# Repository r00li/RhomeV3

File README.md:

Rhome V3
=========

Rhome V3 is a stand-alone ARM based room automation system. It features:

  - (Wireless) Light control
  - Window blind control
  - Local LCD based GUI
  - Wireless remote control (for now 433MHz remotes only)
  - Wifi connectivity
  - Easy to use web control interface (integrated web server)

It runs on a standard STM32F4 Cortex M4 microcontroller. This project includes all the necessary source code (EMBLOCKS PROJECT folder) and eagle board files with schematics (SCHEMATIC folder). I will also add .stl files for a 3D printed case later.

Changelog
----

0.1:

This is an alpha release and needs a lot of code cleanup. More details on how to set eveything up are comming later.

Requirements
-----------

You will need the following things to get this running:

  - A built and ready Rhome V3 PCB (or an STM32F4 discovery board with necessary components connected)
  - A sailwinch servo for each window blind that you want to control (more details are comming later)
  - A wireless 433MHz switch for each light that you want to control (I am using ones made by Intertechno, but others should work)
  - An STM32F4 Discovery board for programming (anything with STLINK should work though)
  - 5V power supply (computer USB port should work though some have trouble powering the PCB with servo motors attached)
  - A running installation of em::blocks IDE (open source, very easy to use) for compiling and uploading the project to the board

After that you just need is to connect your STLINK programmer to the programming interface on the board, select release in the em::blocks IDE and upload the code to the board. All the configuration is done through the integrated GUI.

License
----

GNU GPL v3 - see LICENSE for more details

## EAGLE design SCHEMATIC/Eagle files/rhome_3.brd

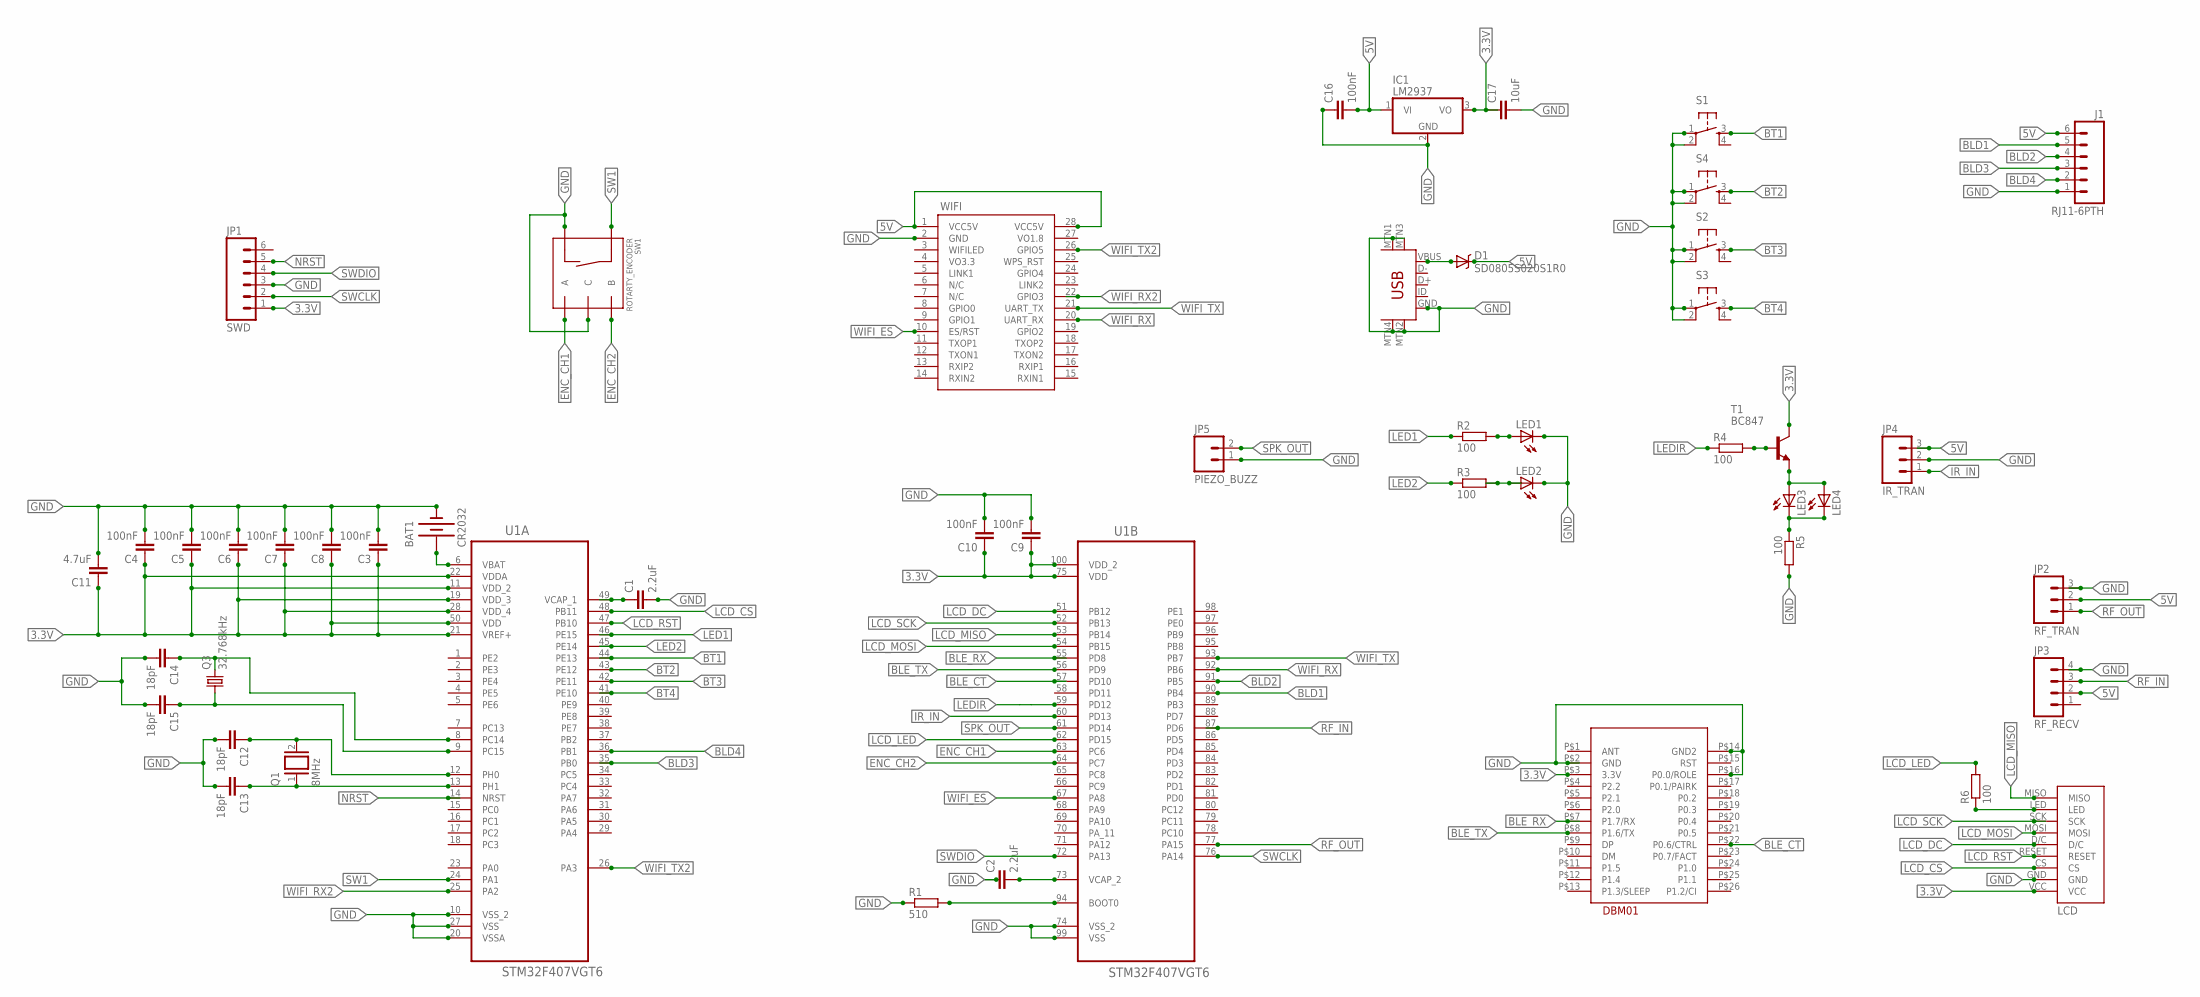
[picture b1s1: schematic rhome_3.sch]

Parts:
BAT1: CR2032; BATTCON_20MM
C1, C2: 2.2uF; 0805
C3, C4, C5, C6, C7, C8, C9, C10, C16: 100nF; 0805
C11: 4.7uF; 0805
C12, C13, C14, C15: 18pF; 0805
C17: 10uF; 0805
D1: SD0805S020S1R0; SOD-323
DBM01: DBM01; SMD
IC1: LM2937; TO263-3
J1: RJ11-6PTH; RJ11-6
JP1: SWD; 1X06
JP2: RF_TRAN; 1X03
JP3: RF_RECV; 1X04
JP4: IR_TRAN; 1X03
JP5: PIEZO_BUZZ; 1X02_LOCK
LCD: ILI9341_SPI_LCD; LCD
LED1, LED2, LED3, LED4: LED5MM
Q1: 8MHz; QS
Q3: 32.768kHz; MC-306
R1: 510; R0805
R2, R3, R4, R5, R6: 100; R0805
S1, S2, S3, S4: TAC_SWITCHPTH; TACTILE-PTH
SW1: ROTARTY_ENCODER; ROTARY_ENC_PLAIN
T1: BC847; SOT23
U1: STM32F407VGT6; QFP50P1600X1600X160-100N
U$1: USB-MINIB-5PIN; USB-MINIB
WIFI: HLK-RM04

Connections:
3.3V: C3.1, C4.1, C5.1, C6.1, C7.1, C8.1, C9.1, C10.1, C11.1, C17.1, DBM01.P$3 (3.3V), IC1.3 (VO), JP1.1, LCD.VCC, T1.3 (C), U1.11 (VDD_2), U1.19 (VDD_3), U1.21 (VREF+), U1.22 (VDDA), U1.28 (VDD_4), U1.50 (VDD), U1.75 (VDD), U1.100 (VDD_2)
5V: C16.2, D1.1 (C), IC1.1 (VI), J1.6, JP2.2, JP3.2, JP4.3, WIFI.1 (VCC5V), WIFI.28 (VCC5V)
BLD1: J1.5, U1.90 (PB4)
BLD2: J1.4, U1.91 (PB5)
BLD3: J1.3, U1.35 (PB0)
BLD4: J1.2, U1.36 (PB1)
BLE_CT: DBM01.P$22 (P0.6/CTRL), U1.57 (PD10)
BLE_RX: DBM01.P$7 (P1.7/RX), U1.55 (PD8)
BLE_TX: DBM01.P$8 (P1.6/TX), U1.56 (PD9)
BT1: S1.3, U1.44 (PE13)
BT2: S4.3, U1.43 (PE12)
BT3: S2.3, U1.42 (PE11)
BT4: S3.3, U1.41 (PE10)
ENC_CH1: SW1.A, U1.63 (PC6)
ENC_CH2: SW1.B, U1.64 (PC7)
GND: BAT1.2 (-), C1.2, C2.1, C3.2, C4.2, C5.2, C6.2, C7.2, C8.2, C9.2, C10.2, C11.2, C12.2, C13.2, C14.2, C15.2, C16.1, C17.2, DBM01.P$2 (GND), DBM01.P$14 (GND2), DBM01.P$16 (P0.0/ROLE), IC1.2 (GND), J1.1, JP1.3, JP2.3, JP3.4, JP4.2, JP5.1, LCD.GND, LED1.K (C), LED2.K (C), R1.1, R5.2, S1.1, S1.2, S2.1, S2.2, S3.1, S3.2, S4.1, S4.2, SW1.C, SW1.SW-, U1.10 (VSS_2), U1.20 (VSSA), U1.27 (VSS), U1.74 (VSS_2), U1.99 (VSS), U$1.GND, U$1.MTN1 (MTN2), U$1.MTN2 (MTN3), U$1.MTN3 (MTN1), U$1.MTN4, WIFI.2 (GND)
IR_IN: JP4.1, U1.60 (PD13)
LCD_CS: LCD.CS, U1.48 (PB11)
LCD_DC: LCD.D/C, U1.51 (PB12)
LCD_LED: R6.2, U1.62 (PD15)
LCD_MISO: LCD.MISO, U1.53 (PB14)
LCD_MOSI: LCD.MOSI, U1.54 (PB15)
LCD_RST: LCD.RESET, U1.47 (PB10)
LCD_SCK: LCD.SCK, U1.52 (PB13)
LED1: R2.1, U1.46 (PE15)
LED2: R3.1, U1.45 (PE14)
LEDIR: R4.1, U1.59 (PD12)
unnamed: C2.2, U1.73 (VCAP_2)
unnamed: C1.1, U1.49 (VCAP_1)
unnamed: C14.1, Q3.4 (2), U1.8 (PC14)
unnamed: C13.1, Q1.1, U1.13 (PH1)
unnamed: C12.1, Q1.2, U1.12 (PH0)
unnamed: C15.1, Q3.1, U1.9 (PC15)
unnamed: D1.2 (A), U$1.VBUS
unnamed: BAT1.1 (+), U1.6 (VBAT)
unnamed: LED1.A, R2.2
unnamed: LED2.A, R3.2
unnamed: R4.2, T1.1 (B)
unnamed: LED3.A, LED4.A, T1.2 (E)
unnamed: R1.2, U1.94 (BOOT0)
unnamed: LED3.K (C), LED4.K (C), R5.1
unnamed: LCD.LED, R6.1
NRST: JP1.5, U1.14 (NRST)
RF_IN: JP3.3, U1.87 (PD6)
RF_OUT: JP2.1, U1.77 (PA15)
SPK_OUT: JP5.2, U1.61 (PD14)
SW1: SW1.SW+, U1.24 (PA1)
SWCLK: JP1.2, U1.76 (PA14)
SWDIO: JP1.4, U1.72 (PA13)
WIFI_ES: U1.67 (PA8), WIFI.10 (ES/RST)
WIFI_RX: U1.92 (PB6), WIFI.20 (UART_RX)
WIFI_RX2: U1.25 (PA2), WIFI.22 (GPIO3)
WIFI_TX: U1.93 (PB7), WIFI.21 (UART_TX)
WIFI_TX2: U1.26 (PA3), WIFI.26 (GPIO5)

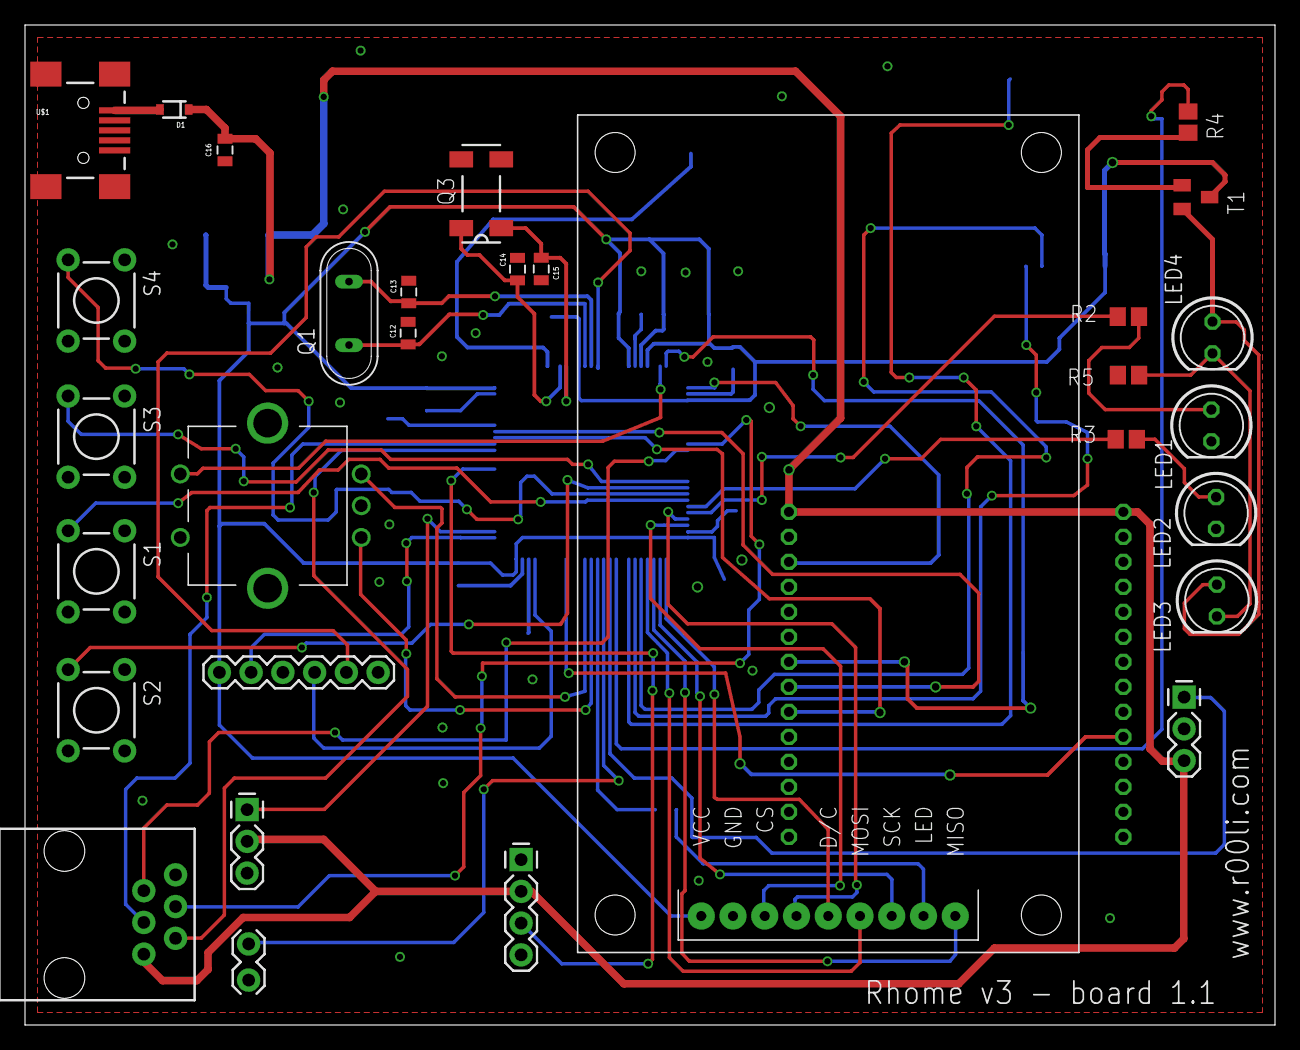
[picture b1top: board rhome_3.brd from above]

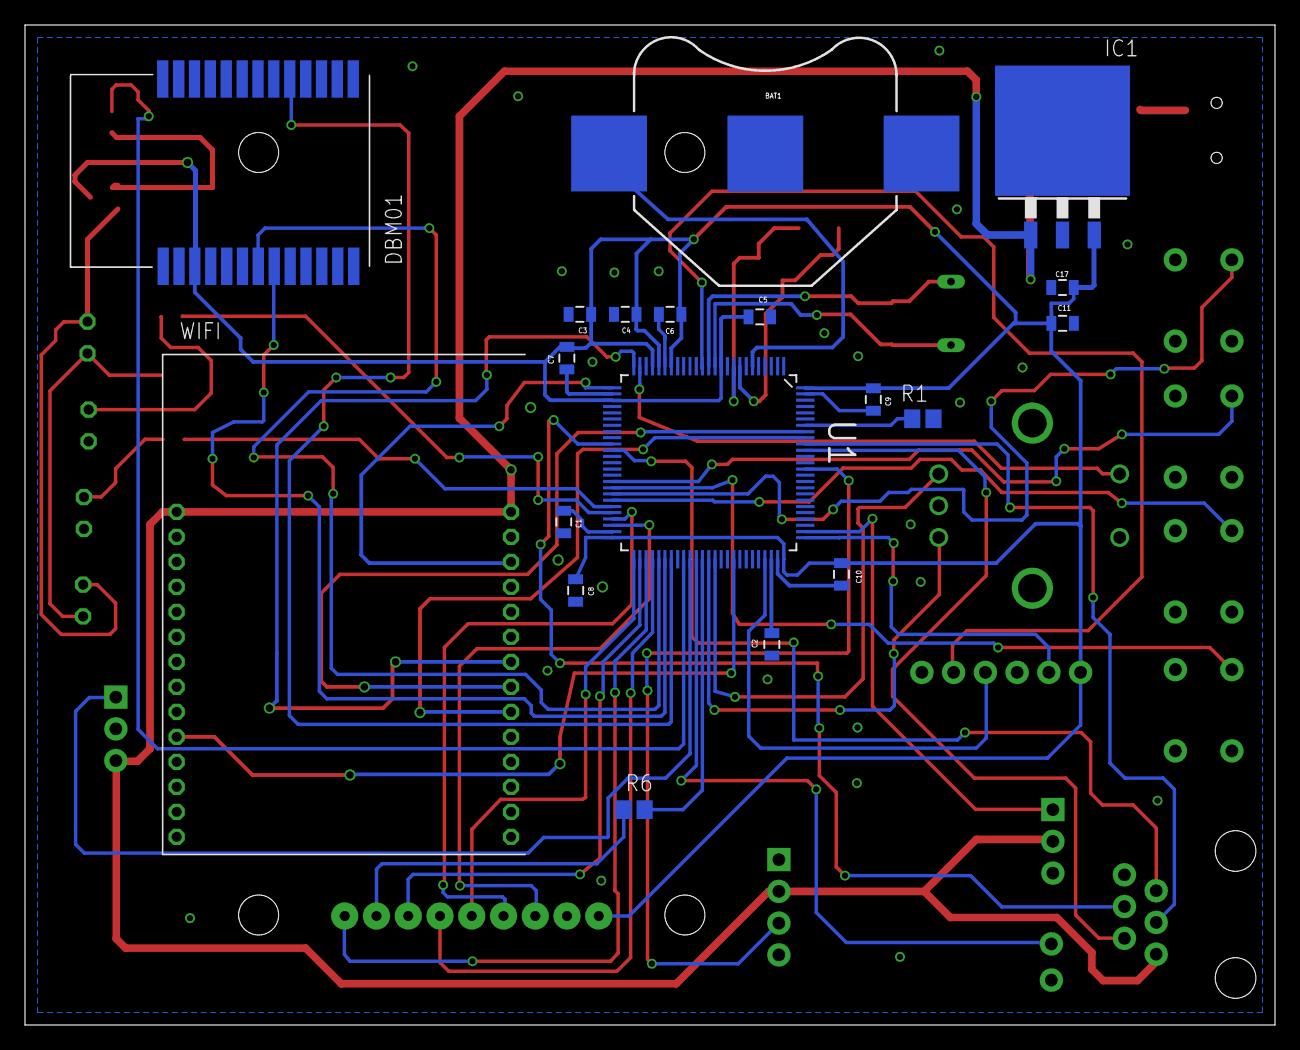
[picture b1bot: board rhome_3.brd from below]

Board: 2 copper layers, 100.0 x 80.0 mm, 49 parts (19 on the bottom side), 54 nets.

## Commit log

2014-09-17 Added complete project source code
2014-09-18 Updated readme file, added schematic files
2015-04-05 Added API support
    Web server now supports API calls.
    It can be reached by URL:port/user/pass/api/
    This will return room status in JSON format.

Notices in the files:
parts and their libraries:
SparkFun-Capacitors: Licensing: CC v3.0 Share-Alike You are welcome to use this library for commercial purposes.
